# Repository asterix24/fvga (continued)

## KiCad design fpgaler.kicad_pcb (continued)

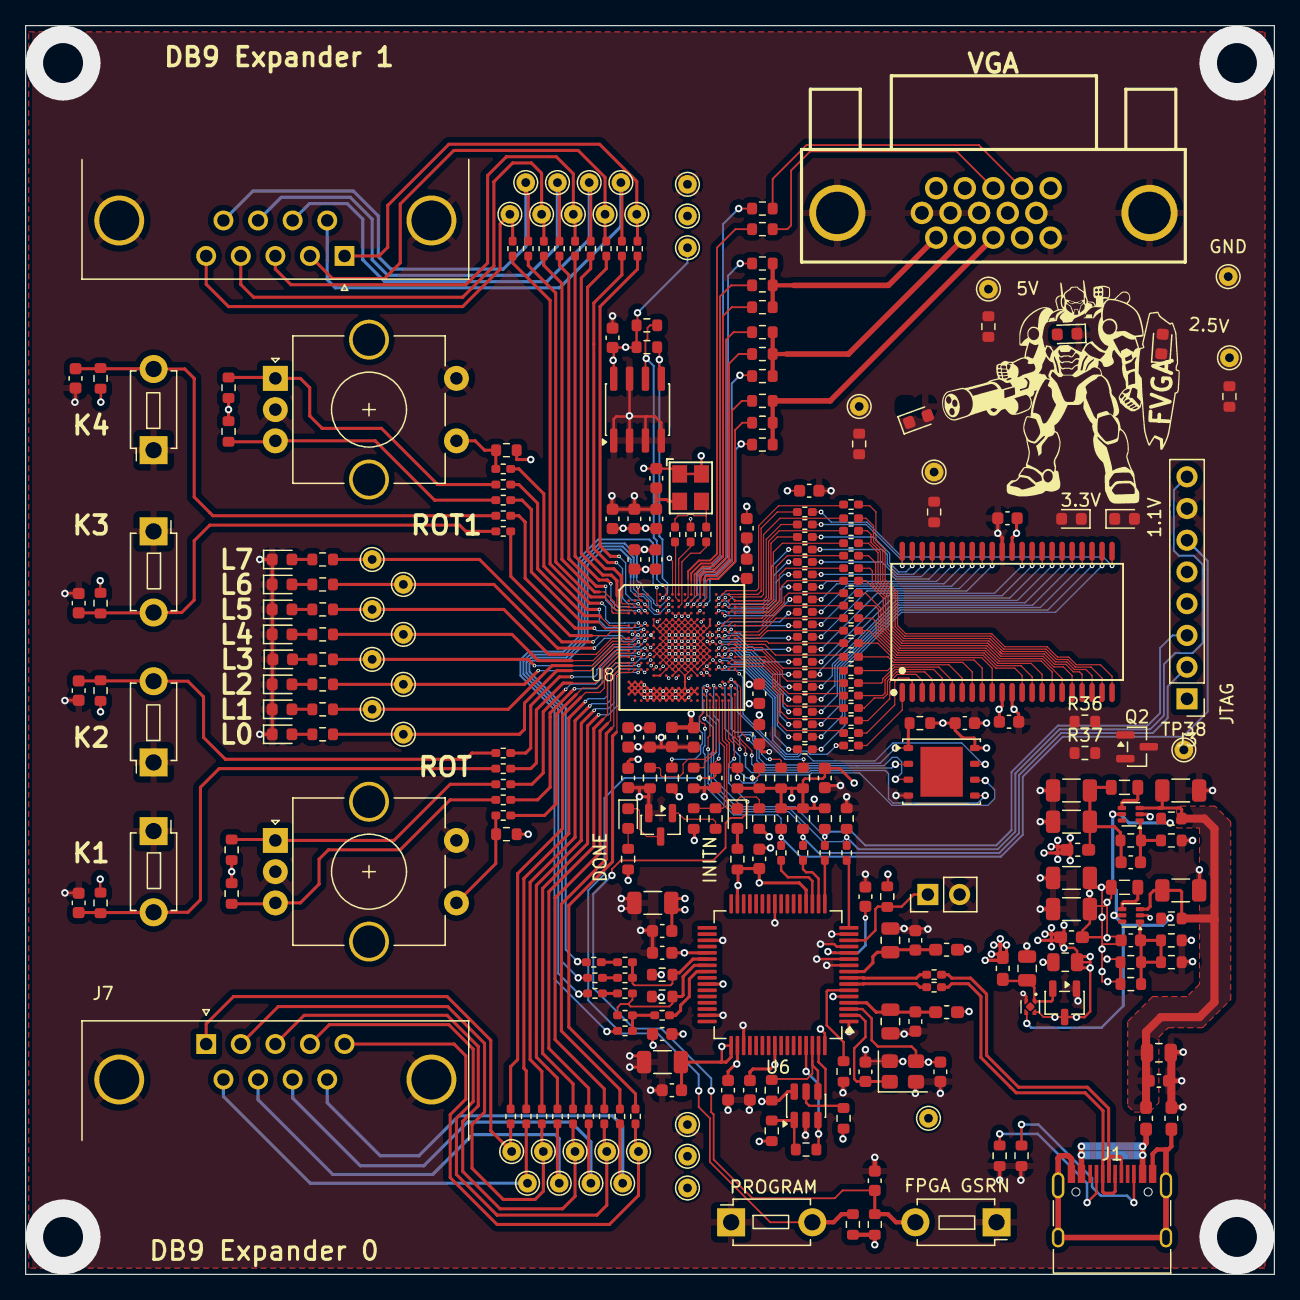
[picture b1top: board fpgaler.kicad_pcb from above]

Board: 4 copper layers, 100.0 x 100.0 mm, 306 parts (0 on the bottom side), 253 nets.

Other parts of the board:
C22, C26, C27, C28, C29, C30, C31, C32, C34, C35: 100nF; C_0603_1608Metric
C23, C24: 18pF; C_0603_1608Metric
C25, C33: 10uF; C_1206_3216Metric
C36, C37: 4.7uF; C_0805_2012Metric
FB2, FB3: 15Ω@100MHz; L_0603_1608Metric_Pad1.05x0.95mm_HandSolder
R44, R45, R46: 10k; R_0603_1608Metric
R47, R50: 12k; R_0603_1608Metric
R48, R51, R58, R62: 2.2k; R_0603_1608Metric
R52, R53, R54, R55, R56, R57, R59, R60, R61: 22R; R_0402_1005Metric_Pad0.72x0.64mm_HandSolder
R63, R64, R65: 4.7k; R_0603_1608Metric
U5: 93LC56BT-I/OT; SOT-23-6
U6: FT2232HL; LQFP-64_10x10mm_P0.5mm
Y1: 7M-12.000MAAJ; Oscillator_SMD_Abracon_ASE-4Pin_3.2x2.5mm

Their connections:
+3.3V: C22.1, C28.1, C30.1, C31.1, C32.1, C33.2, FB2.2, FB3.2, R44.1, R45.2, R46.2, R48.1, R51.2, R58.2, R63.1, R64.1, R65.1, U5.6 (VCC), U6.20 (VCCIO), U6.31 (VCCIO), U6.42 (VCCIO), U6.50 (VREGIN), U6.56 (VCCIO); also elsewhere on the board
/FPGA/RXD_UART: R57.2; also elsewhere on the board
/FPGA/SCL0: R59.2; also elsewhere on the board
/FPGA/SDA0: R60.2, R61.2; also elsewhere on the board
/FPGA/TXD_UART: R56.2; also elsewhere on the board
/FTDI/12MHz: C24.1, U6.3 (OSCO), Y1.3; also elsewhere on the board
/FTDI/D_N: U6.7 (DM); also elsewhere on the board
/FTDI/D_P: U6.8 (DP); also elsewhere on the board
/FTDI/FT_RESET: R48.2, U6.14 (~RESET); also elsewhere on the board
/FTDI/V_PHY: C34.1, C36.1, FB2.1, U6.4 (VPHY)
/FTDI/V_PLL: C35.1, C37.1, FB3.1, U6.9 (VPLL)
/FT_TCK: R52.2, R62.2; also elsewhere on the board
/FT_TDI: R53.2, R63.2; also elsewhere on the board
/FT_TDO: R54.2, R64.2; also elsewhere on the board
/FT_TMS: R55.2, R65.2; also elsewhere on the board
EE_CLK: R45.1, U5.4 (CLK), U6.62 (EECLK)
EE_CS: R44.2, U5.5 (CS), U6.63 (EECS)
EE_DAT: R47.1, U5.3 (DI), U6.61 (EEDATA)
GND: C22.2, C23.2, C24.2, C25.1, C26.2, C27.2, C28.2, C29.2, C30.2, C31.2, C32.2, C33.1, C34.2, C35.2, C36.2, C37.2, R50.2, R62.1, U5.2 (GND), U6.1 (GND), U6.5 (GND), U6.10 (AGND), U6.11 (GND), U6.13 (TEST), U6.15 (GND), U6.25 (GND), U6.35 (GND), U6.47 (GND), U6.51 (GND), Y1.2 (G), Y1.4 (G); also elsewhere on the board
unnamed: R46.1, R47.2, U5.1 (DO)
unnamed: R52.1, U6.16 (ADBUS0)
unnamed: R53.1, U6.17 (ADBUS1)
unnamed: R54.1, U6.18 (ADBUS2)
unnamed: R55.1, U6.19 (ADBUS3)
unnamed: R56.1, R58.1, R59.1, U6.38 (BDBUS0)
unnamed: R51.1, R57.1, R60.1, U6.39 (BDBUS1)
unnamed: R61.1, U6.40 (BDBUS2)
unnamed: C23.1, U6.2 (OSCI), Y1.1
unnamed: R50.1, U6.6 (REF)
VCC1_8FT: C25.2, C26.1, C27.1, C29.1, U6.12 (VCORE), U6.37 (VCORE), U6.49 (VREGOUT), U6.64 (VCORE)

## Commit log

2026-03-04 Continue routing
2026-03-05 Place planes
2026-03-09 Plase silkscreen
2026-03-09 Start to fix dcr
2026-03-10 Add output files
2026-03-10 Add imported lib
2026-03-10 change tactile button, update output files
